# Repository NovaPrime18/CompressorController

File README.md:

# Mains Powered Motor Driver

> **HVAC VESC** — A mains-powered, VESC-compatible three-phase motor driver with active Power Factor Correction, built for compressor and HVAC applications.

---

<table><tr>
<td></td>
<td></td>
</tr></table>

---

## Overview

This project is an open-hardware, mains-powered (230 V AC) three-phase motor driver that is fully compatible with the [VESC firmware](https://vesc-project.com/) ecosystem. It targets compressor and HVAC drive applications and is designed with grid compliance in mind, featuring active Power Factor Correction (PFC) to meet IEC 61000-3-2 harmonic emission limits.

The board takes 230 V AC directly from the mains, rectifies it to a high-voltage DC bus, and drives a three-phase motor through an Infineon IKCM10H60 Intelligent Power Module. A VESC Express (ESP32) module provides wireless connectivity and acts as the CAN/Wi-Fi/BT bridge, while an STM32F405 runs the VESC motor-control firmware.

---

## Key Features

| Feature | Details |
|---|---|
| **Input** | 230 V AC single-phase mains |
| **HV Bus** | Rectified DC bus (~325 V DC nominal) |
| **Power Bridge** | Infineon `IKCM10H60GAXKMA1` IPM — 10 A / 600 V, integrated gate drivers & bootstrap |
| **Active PFC** | Texas Instruments `UCC28180D` — CCM PFC controller |
| **MCU** | STMicroelectronics `STM32F405RGTx` running VESC firmware |
| **Connectivity** | VESC Express (ESP32) — Wi-Fi, Bluetooth & CAN bridge |
| **USB** | USB Type-C (programming / configuration) |
| **CAN Bus** | Dual isolated CAN interfaces |
| **Debug** | Tag-Connect SWD header |
| **Status LEDs** | Red & Green indicators |
| **License** | CERN Open Hardware Licence v2 |

---

## Block Diagram

```
         230 V AC
             │
     ┌───────▼────────┐
     │   Power in     │  EMI filter, inrush, rectifier
     │  (powerin.sch) │
     └───────┬────────┘
             │ HV DC Bus (~325 V)
     ┌───────▼────────┐
     │   Active PFC   │  UCC28180D — CCM boost PFC
     │   (pfc.sch)    │  IEC 61000-3-2 compliant
     └───────┬────────┘
             │ Regulated HV Bus
     ┌───────▼────────┐
     │  3-Phase IPM   │  IKCM10H60GAXKMA1
     │  (phases.sch)  │  10 A / 600 V, 3-phase bridge
     └───────┬────────┘
             │ U / V / W
          Motor / Compressor

     ┌──────────────────────────────────────────┐
     │              Control Domain              │
     │                                          │
     │  STM32F405  ◄──►  Isolator  ◄──►  IPM   │
     │  (VESC FW)        (iso.sch)    gate sigs │
     │      │                                   │
     │  Filters ── Current U/V/W sensing        │
     │  (filters)  Bus voltage / Phase voltages │
     │      │                                   │
     │  VESC Express (ESP32) ── CAN / BT / WiFi │
     │  LV Power ── 3.3 V / 5 V rails          │
     └──────────────────────────────────────────┘
```

---

## Schematic Hierarchy

The design is split into focused sub-sheets for clarity and reuse:

| Sheet | File | Description |
|---|---|---|
| Top-level | `CompressorController.kicad_sch` | Connectors, indicators, sheet assembly |
| MCU | `MCU.kicad_sch` | STM32F405RGTx, crystal, decoupling, SWD |
| PFC | `pfc.kicad_sch` | UCC28180D active PFC stage |
| Power in | `powerin.kicad_sch` | Mains input, EMI filter, bridge rectifier |
| Phases | `phases.kicad_sch` | IKCM10H60 IPM, current sensing |
| Filters | `filters.kicad_sch` | ADC anti-aliasing for current & voltage signals |
| Isolator | `isolator.kicad_sch` | Gate-signal and fault isolation barrier |
| LV Power | `lvpower.kicad_sch` | 3.3 V / 5 V low-voltage power supply |
| WiFi & BT | `express.kicad_sch` | VESC Express (ESP32) module |
| CAN | `can.kicad_sch` | Isolated CAN transceivers |

---

## Firmware

This board is designed to run the open-source **VESC firmware** and is configurable via **VESC Tool**.

- [VESC Firmware](https://github.com/vedderb/bldc)
- [VESC Tool](https://vesc-project.com/vesc_tool)

Motor parameters, PID gains, current limits, and field-weakening are all configured through VESC Tool over USB-C or wirelessly via the onboard VESC Express (Wi-Fi / BLE).

---

## Regulatory Compliance Targets

This design is being developed with the following standards in scope:

| Standard | Scope |
|---|---|
| **IEC 61000-3-2** | Harmonic current emission limits *(primary — addressed by active PFC)* |
| **IEC 60335-2-34** | Particular requirements for motor-compressors |
| **EN IEC 63000** | RoHS technical documentation |

> ⚠️ **Note:** This is an open hardware design. Regulatory certification (CE marking) must be obtained by the integrating party before placing the product on the EU market. The presence of PFC significantly aids IEC 61000-3-2 Class A/D compliance but does not guarantee it without verified measurement.

---

## Safety Warnings

> **⚡ HIGH VOLTAGE — MAINS POWERED**
>
> This board operates at lethal voltages. The HV DC bus reaches approximately **325–400 V DC** from rectified mains. Do **not** touch the board while powered. Ensure adequate enclosure, creepage/clearance distances, and fusing when integrating into a product. Only qualified persons should work on mains-connected equipment.

---

## License

This project is released under the **CERN Open Hardware Licence Version 2 – Strongly Reciprocal (CERN-OHL-S v2)**.

You may study, modify, and distribute this design, provided that any derivative works are released under the same licence and that attribution to the original authors is maintained.

© Picobello B.V. — see [`LICENSE`](LICENSE) for full terms.

---

## Contributing

Issues, improvements, and pull requests are welcome. Please open an issue before submitting large changes so the direction can be aligned first.

When contributing hardware changes, include updated schematics (KiCad 10 `.kicad_sch` format) and a description of what was changed and why.

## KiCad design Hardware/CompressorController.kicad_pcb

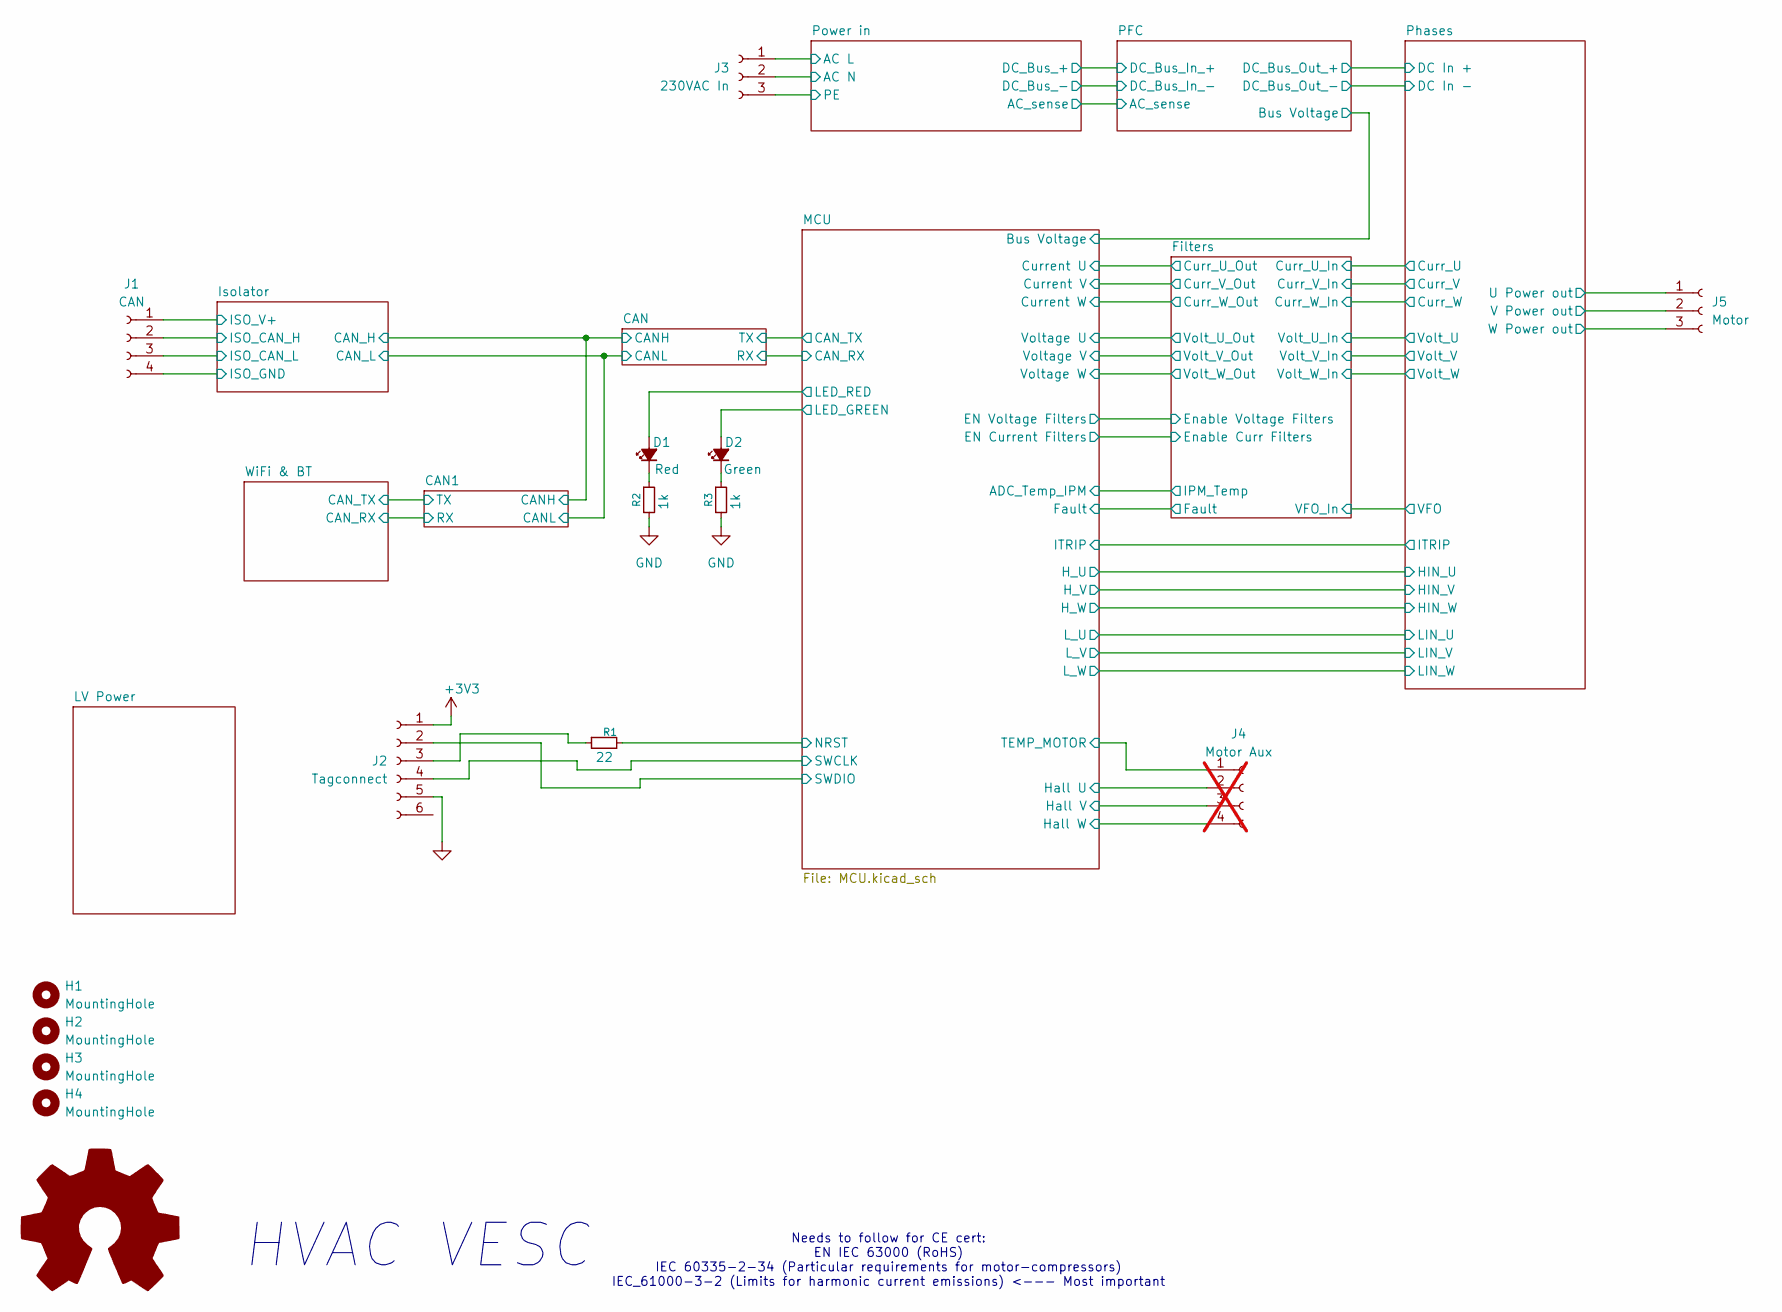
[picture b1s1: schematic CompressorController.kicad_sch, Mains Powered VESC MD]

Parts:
D1: Red; LED_0603_1608Metric; LCSC C2286
D2: Green; LED_0603_1608Metric; LCSC C84267
H1, H2, H3, H4: MountingHole; MountingHole_3.2mm_M3
J1: CAN; PhoenixContact_MC_1,5_4-G-3.5_1x04_P3.50mm_Horizontal; JLC C395831
J2: Tagconnect; Tag-Connect_TC2030-IDC-NL_2x03_P1.27mm_Vertical
J3: 230VAC In; PhoenixContact_GMSTB_2,5_3-GF-7,62_1x03_P7.62mm_Horizontal_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; JLC C5121957
J4: Motor Aux; PhoenixContact_MC_1,5_4-G-3.5_1x04_P3.50mm_Horizontal; JLC C395831; not fitted
J5: Motor; PhoenixContact_GMSTB_2,5_3-GF-7,62_1x03_P7.62mm_Horizontal_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; JLC C5121957
R1: 22; R_0603_1608Metric; LCSC C23345
R2, R3: 1k; R_0603_1608Metric; LCSC C21190

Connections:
+3V3: J2.1; also elsewhere on the board
/Isolator/ISO_CAN_H: J1.2; also elsewhere on the board
/Isolator/ISO_CAN_L: J1.3; also elsewhere on the board
/Isolator/ISO_GND: J1.4; also elsewhere on the board
/Isolator/ISO_V+: J1.1; also elsewhere on the board
/MCU/LED_GREEN: D2.2 (A); also elsewhere on the board
/MCU/LED_RED: D1.2 (A); also elsewhere on the board
/MCU/NRST: R1.2; also elsewhere on the board
/MCU/SWCLK: J2.4; also elsewhere on the board
/MCU/SWDIO: J2.2; also elsewhere on the board
/Phases/U Power out: J5.1; also elsewhere on the board
/Phases/V Power out: J5.2; also elsewhere on the board
/Phases/W Power out: J5.3; also elsewhere on the board
/Power in/AC L: J3.1; also elsewhere on the board
/Power in/AC N: J3.2; also elsewhere on the board
Earth_Protective: J3.3; also elsewhere on the board
GND: J2.5, R2.2, R3.2; also elsewhere on the board
unnamed: D1.1 (K), R2.1
unnamed: D2.1 (K), R3.1
unnamed: J2.3, R1.1

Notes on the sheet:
HVAC VESC
Needs to follow for CE cert: EN IEC 63000 (RoHS) IEC 60335-2-34 (Particular requirements for motor-compressors) IEC_61000-3-2 (Limits for harmonic current emissions) <--- Most important

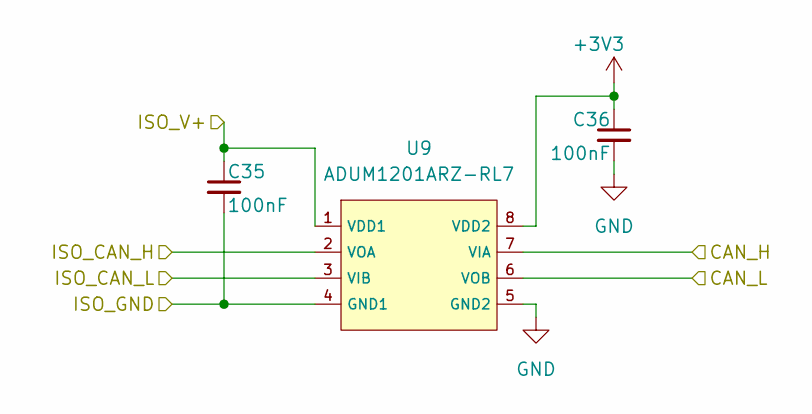
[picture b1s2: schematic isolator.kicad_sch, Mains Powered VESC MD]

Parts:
C35, C36: 100nF; C_0603_1608Metric; LCSC C14663
U9: ADUM1201ARZ-RL7; SOIC-8_L4.9-W3.9-P1.27-LS6.0-BL; Part ADUM1201ARZ-RL7; LCSC C9669

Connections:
+3V3: C36.1, U9.8 (VDD2); also elsewhere on the board
/CAN/CANH: U9.7 (VIA); also elsewhere on the board
/CAN/CANL: U9.6 (VOB); also elsewhere on the board
/Isolator/ISO_CAN_H: U9.2 (VOA); also elsewhere on the board
/Isolator/ISO_CAN_L: U9.3 (VIB); also elsewhere on the board
/Isolator/ISO_GND: C35.2, U9.4 (GND1); also elsewhere on the board
/Isolator/ISO_V+: C35.1, U9.1 (VDD1); also elsewhere on the board
GND: C36.2, U9.5 (GND2); also elsewhere on the board

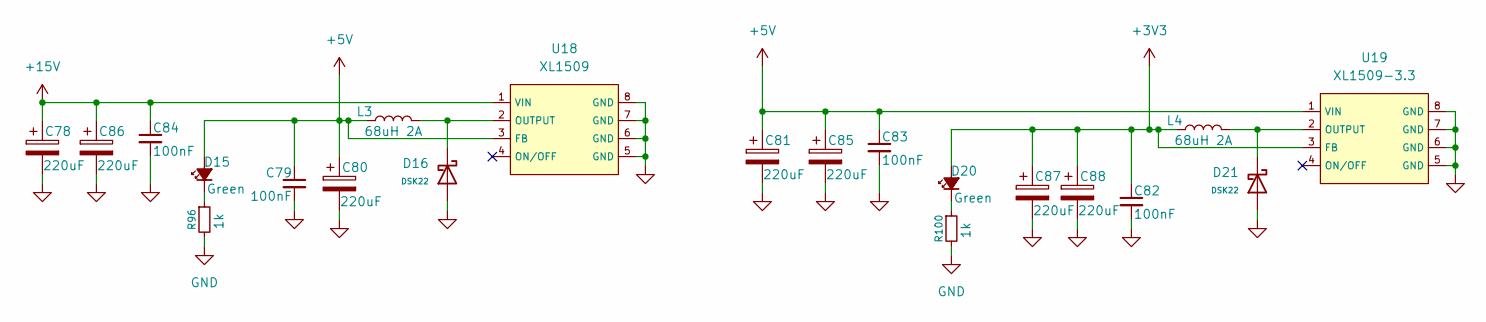
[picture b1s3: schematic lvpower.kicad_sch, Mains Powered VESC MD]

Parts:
C78, C80, C81, C85, C86, C87, C88: 220uF; CP_Elec_8x10.5; Voltage 50V; JLC C3340
C79, C82, C83, C84: 100nF; C_0603_1608Metric; LCSC C14663
D15, D20: Green; LED_0603_1608Metric; LCSC C84267
D16, D21: DSK22; D_SOD-123FL; Forward Voltage (Vf@If) 550mV@2A; Reverse Voltage (Vr) 20V; Part DSK22; LCSC C28646290
L3, L4: 68uH 2A; L_KOHERelec_MDA7030; JLC C2894721
R96, R100: 1k; R_0603_1608Metric; LCSC C21190
U18: XL1509; SOIC-8_L5.0-W4.0-P1.27-LS6.0-BL; Output Voltage 5V; Input Voltage 4.5V~40V; Part XL1509-5.0E1; LCSC C61063
U19: XL1509-3.3; SOIC-8_L5.0-W4.0-P1.27-LS6.0-BL; Output Voltage 3.3V; Input Voltage 4.5V~40V; Part XL1509-5.0E1; LCSC C2681226

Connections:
+3V3: C82.1, C87.1, C88.1, D20.2 (A), L4.1, U19.3 (FB); also elsewhere on the board
+5V: C79.1, C80.1, C81.1, C83.1, C85.1, D15.2 (A), L3.1, U18.3 (FB), U19.1 (VIN); also elsewhere on the board
+15V: C78.1, C84.1, C86.1, U18.1 (VIN); also elsewhere on the board
GND: C78.2, C79.2, C80.2, C81.2, C82.2, C83.2, C84.2, C85.2, C86.2, C87.2, C88.2, D16.2, D21.2, R96.2, R100.2, U18.5 (GND), U18.6 (GND), U18.7 (GND), U18.8 (GND), U19.5 (GND), U19.6 (GND), U19.7 (GND), U19.8 (GND); also elsewhere on the board
unnamed: D15.1 (K), R96.1
unnamed: D20.1 (K), R100.1
unnamed: D16.1, L3.2, U18.2 (OUTPUT)
unnamed: D21.1, L4.2, U19.2 (OUTPUT)

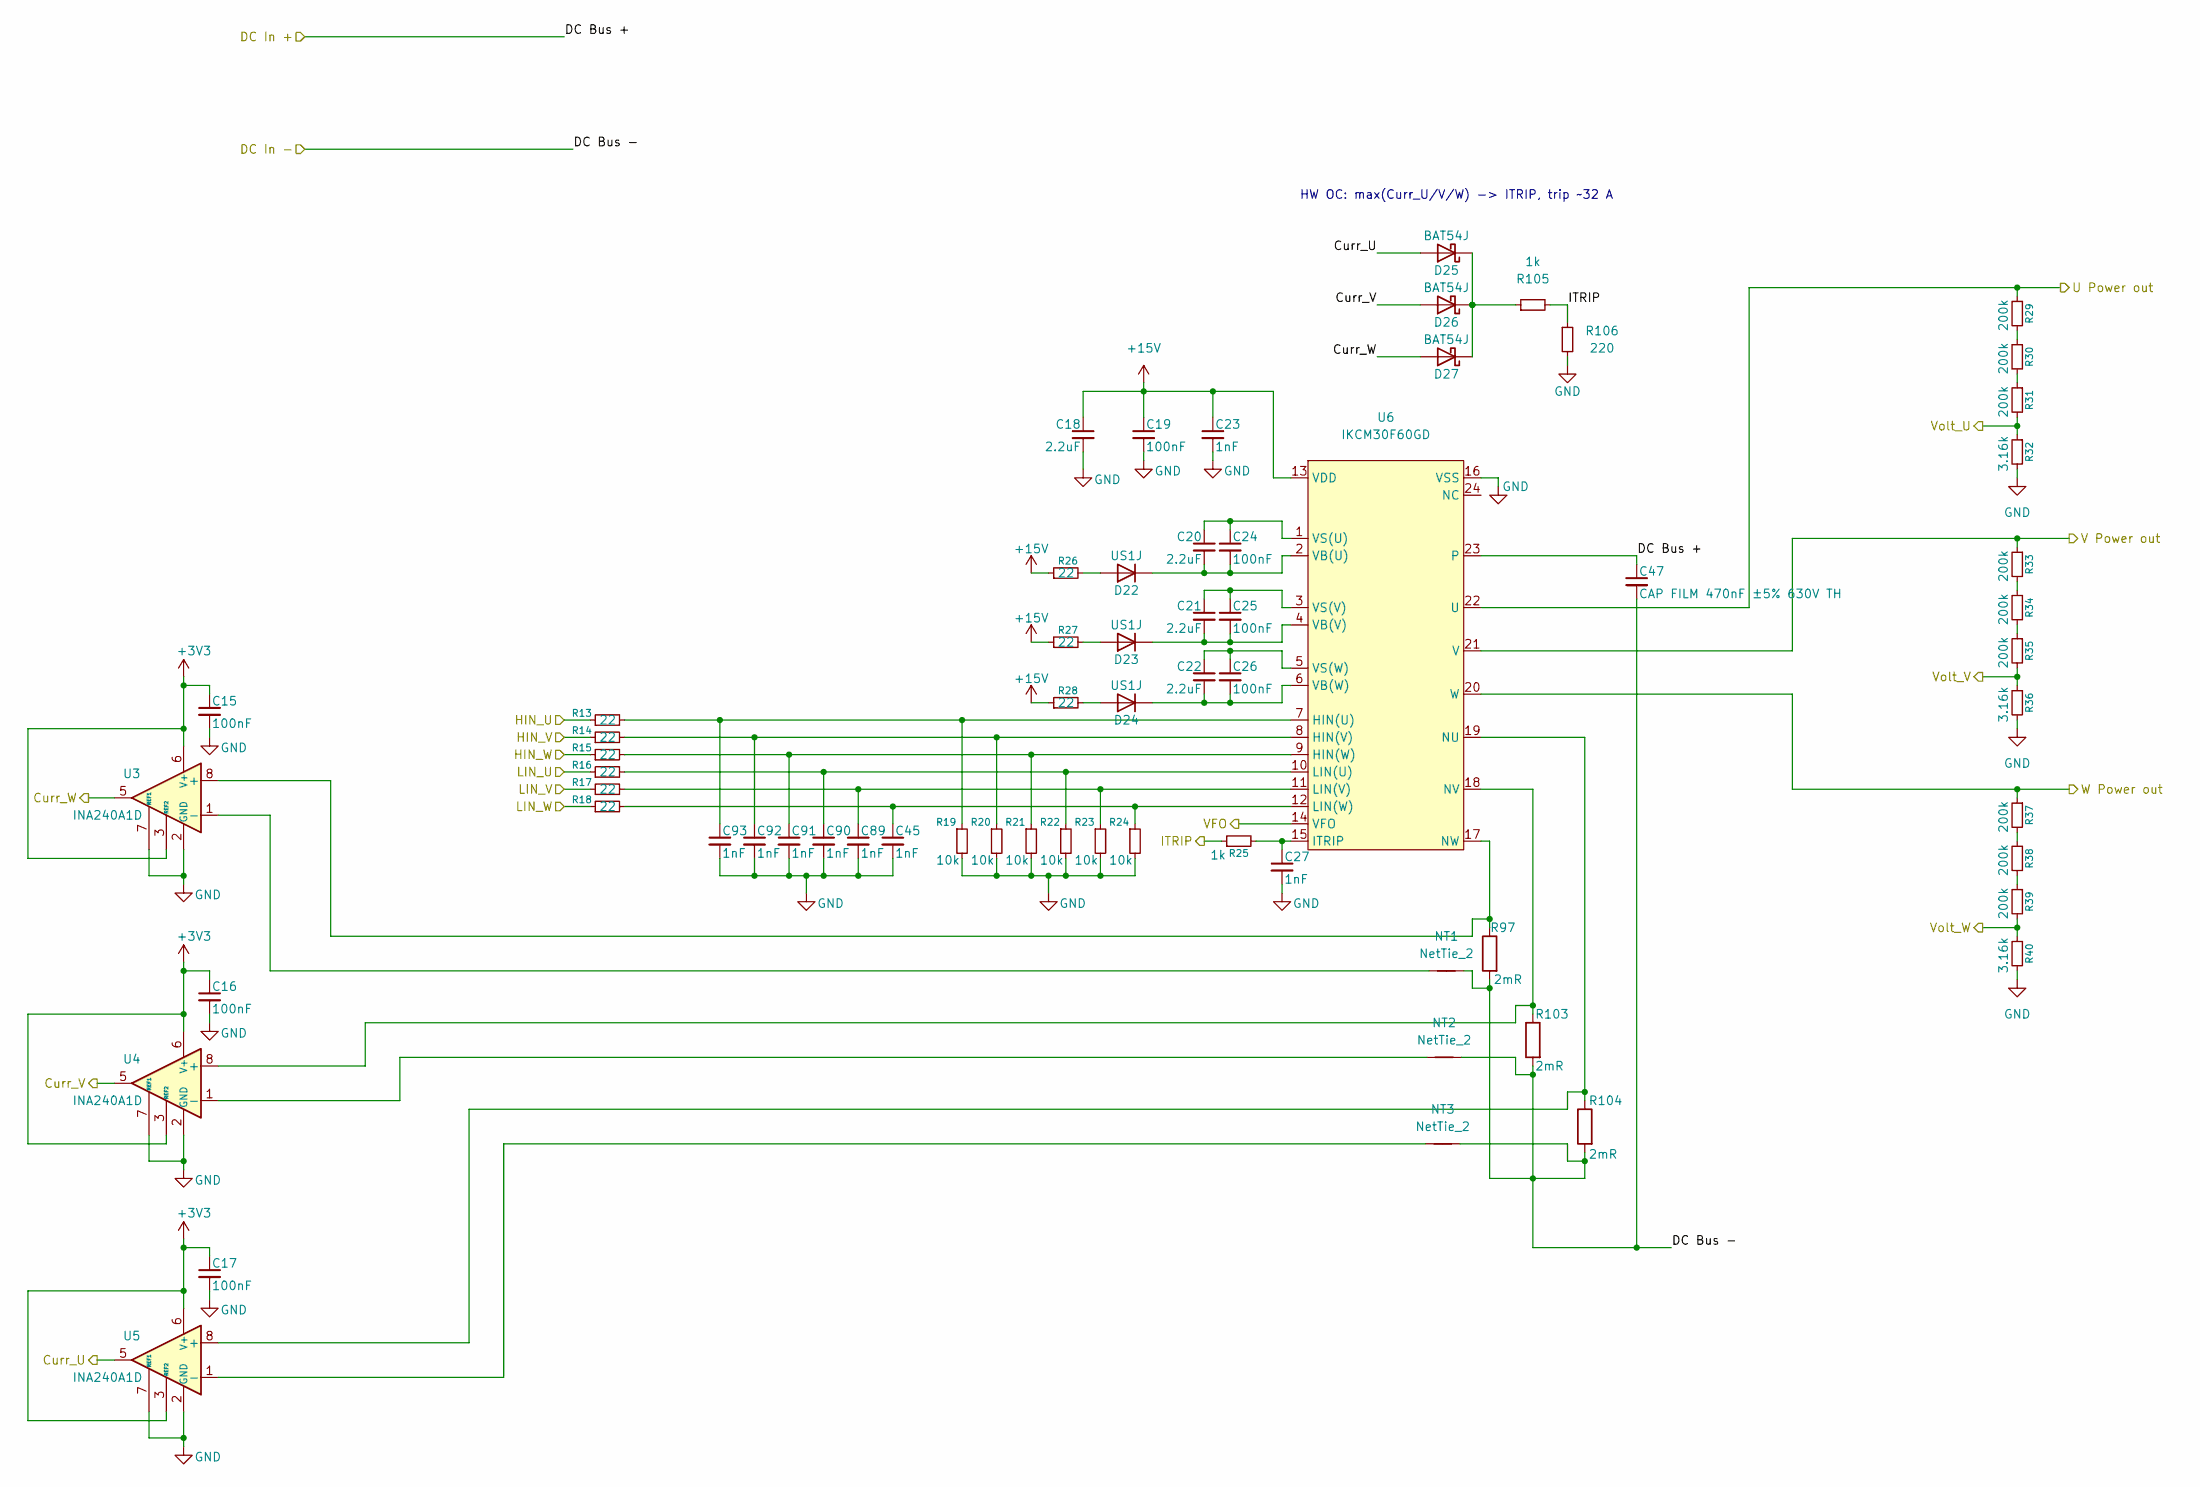
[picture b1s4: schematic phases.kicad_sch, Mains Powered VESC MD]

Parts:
C15, C16, C17, C19, C24, C25, C26: 100nF; C_0603_1608Metric; LCSC C14663
C18, C20, C21, C22: 2.2uF; C_1206_3216Metric; LCSC C50254
C23, C27, C45, C89, C90, C91, C92, C93: 1nF; C_0603_1608Metric; LCSC C1588
C47: CAP FILM 470nF ±5% 630V TH; C_Rect_L26.5mm_W11.5mm_P22.50mm_MKS4; Voltage 630V; LCSC C3796047
D22, D23, D24: US1J; D_SMA; LCSC C44763
D25, D26, D27: BAT54J; D_SOD-323F; LCSC C12744
NT1, NT2, NT3: NetTie_2; NetTie-2_SMD_Pad0.5mm
R13, R14, R15, R16, R17, R18, R26, R27, R28: 22; R_0603_1608Metric; LCSC C23345
R19, R20, R21, R22, R23, R24: 10k; R_0603_1608Metric; LCSC C25804
R25, R105: 1k; R_0603_1608Metric; LCSC C21190
R29, R30, R31, R33, R34, R35, R37, R38, R39: 200k; R_1206_3216Metric; LCSC C17954
R32, R36, R40: 3.16k; R_0805_2012Metric; LCSC C52603
R97, R103, R104: 2mR; R_1206_3216Metric; JLC C2904210
R106: 220; R_0603_1608Metric; LCSC C22962
U3, U4, U5: INA240A1D; SOIC-8_3.9x4.9mm_P1.27mm; LCSC C1346458
U6: IKCM30F60GD; DIP-24_L36.0-W21.0-P1.60-LS28.6-TL; LCSC Part C476130

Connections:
+3V3: C15.1, C16.1, C17.1, U3.3 (REF2), U3.6 (V+), U4.3 (REF2), U4.6 (V+), U5.3 (REF2), U5.6 (V+); also elsewhere on the board
+15V: C18.1, C19.1, C23.1, R26.1, R27.1, R28.1, U6.13 (VDD); also elsewhere on the board
/Filters/VFO_In: U6.14 (VFO); also elsewhere on the board
/Filters/Volt_U_In: R31.2, R32.1; also elsewhere on the board
/Filters/Volt_V_In: R35.2, R36.1; also elsewhere on the board
/Filters/Volt_W_In: R39.2, R40.1; also elsewhere on the board
/MCU/H_U: R13.1; also elsewhere on the board
/MCU/H_V: R14.1; also elsewhere on the board
/MCU/H_W: R15.1; also elsewhere on the board
/MCU/L_U: R16.1; also elsewhere on the board
/MCU/L_V: R17.1; also elsewhere on the board
/MCU/L_W: R18.1; also elsewhere on the board
/Phases/Curr_U: D25.2 (A), U5.5; also elsewhere on the board
/Phases/Curr_V: D26.2 (A), U4.5; also elsewhere on the board
/Phases/Curr_W: D27.2 (A), U3.5; also elsewhere on the board
/Phases/DC Bus +: C47.1, U6.23; also elsewhere on the board
/Phases/ITRIP: R25.1, R105.2, R106.1; also elsewhere on the board
/Phases/U Power out: R29.1, U6.22 (U); also elsewhere on the board
/Phases/V Power out: R33.1, U6.21 (V); also elsewhere on the board
/Phases/W Power out: R37.1, U6.20 (W); also elsewhere on the board
GND: C15.2, C16.2, C17.2, C18.2, C19.2, C23.2, C27.2, C45.2, C47.2, C89.2, C90.2, C91.2, C92.2, C93.2, NT1.2, NT2.2, NT3.2, R19.2, R20.2, R21.2, R22.2, R23.2, R24.2, R32.2, R36.2, R40.2, R97.2, R103.2, R104.2, R106.2, U3.2 (GND), U3.4 (GND), U3.7 (REF1), U4.2 (GND), U4.4 (GND), U4.7 (REF1), U5.2 (GND), U5.4 (GND), U5.7 (REF1), U6.16 (VSS); also elsewhere on the board
unnamed: D22.2 (A), R26.2
unnamed: C20.2, C24.2, D22.1 (K), U6.2 (VB(U))
unnamed: D23.2 (A), R27.2
unnamed: C21.2, C25.2, D23.1 (K), U6.4 (VB(V))
unnamed: D24.2 (A), R28.2
unnamed: C22.2, C26.2, D24.1 (K), U6.6 (VB(W))
unnamed: D25.1 (K), D26.1 (K), D27.1 (K), R105.1
unnamed: R29.2, R30.1
unnamed: R30.2, R31.1
unnamed: R33.2, R34.1
unnamed: R34.2, R35.1
unnamed: R37.2, R38.1
unnamed: R38.2, R39.1
unnamed: R97.1, U3.8 (+), U6.17 (NW)
unnamed: NT1.1, U3.1 (-)
unnamed: R103.1, U4.8 (+), U6.18 (NV)
unnamed: NT2.1, U4.1 (-)
unnamed: R104.1, U5.8 (+), U6.19 (NU)
unnamed: NT3.1, U5.1 (-)
unnamed: C93.1, R13.2, R19.1, U6.7 (HIN(U))
unnamed: C92.1, R14.2, R20.1, U6.8 (HIN(V))
unnamed: C91.1, R15.2, R21.1, U6.9 (HIN(W))
unnamed: C27.1, R25.2, U6.15 (ITRIP)
unnamed: C90.1, R16.2, R22.1, U6.10 (LIN(U))
unnamed: C89.1, R17.2, R23.1, U6.11 (LIN(V))
unnamed: C45.1, R18.2, R24.1, U6.12 (LIN(W))
unnamed: C20.1, C24.1, U6.1 (VS(U))
unnamed: C21.1, C25.1, U6.3 (VS(V))
unnamed: C22.1, C26.1, U6.5 (VS(W))

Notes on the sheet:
HW OC: max(Curr_U/V/W) -> ITRIP, trip ~32 A

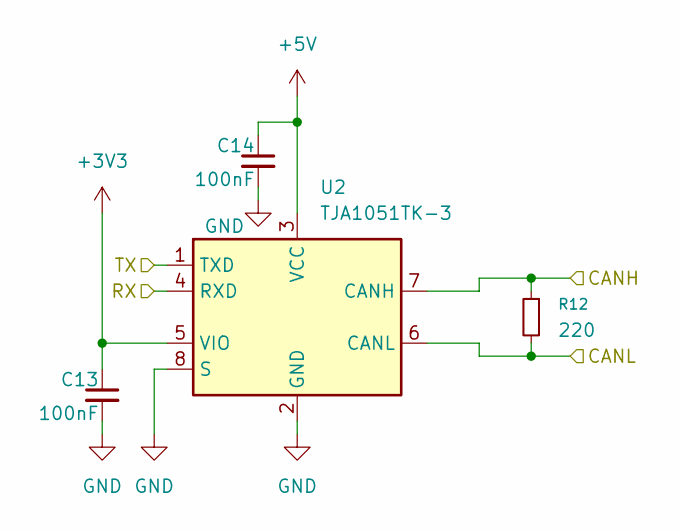
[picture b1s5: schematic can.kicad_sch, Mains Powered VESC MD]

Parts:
C13, C14: 100nF; C_0603_1608Metric; LCSC C14663
R12: 220; R_0603_1608Metric; LCSC C22962
U2: TJA1051TK-3; HVSON-8-1EP_3x3mm_P0.65mm_EP1.6x2.4mm; JLC C2875699

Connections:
+3V3: C13.1, U2.5 (VIO); also elsewhere on the board
+5V: C14.1, U2.3 (VCC); also elsewhere on the board
/CAN1/RX: U2.4 (RXD); also elsewhere on the board
/CAN1/TX: U2.1 (TXD); also elsewhere on the board
/CAN/CANH: R12.1, U2.7 (CANH); also elsewhere on the board
/CAN/CANL: R12.2, U2.6 (CANL); also elsewhere on the board
GND: C13.2, C14.2, U2.2 (GND), U2.8 (S), U2.9 (GND); also elsewhere on the board

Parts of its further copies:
C29, C30: 100nF; C_0603_1608Metric; LCSC C14663
R41: 220; R_0603_1608Metric; LCSC C22962
U7: TJA1051TK-3; HVSON-8-1EP_3x3mm_P0.65mm_EP1.6x2.4mm; JLC C2875699

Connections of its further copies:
+3V3: C29.1, U7.5 (VIO); also elsewhere on the board
+5V: C30.1, U7.3 (VCC); also elsewhere on the board
/CAN/CANH: R41.1, U7.7 (CANH); also elsewhere on the board
/CAN/CANL: R41.2, U7.6 (CANL); also elsewhere on the board
/CAN/RX: U7.4 (RXD); also elsewhere on the board
/CAN/TX: U7.1 (TXD); also elsewhere on the board
GND: C29.2, C30.2, U7.2 (GND), U7.8 (S), U7.9 (GND); also elsewhere on the board

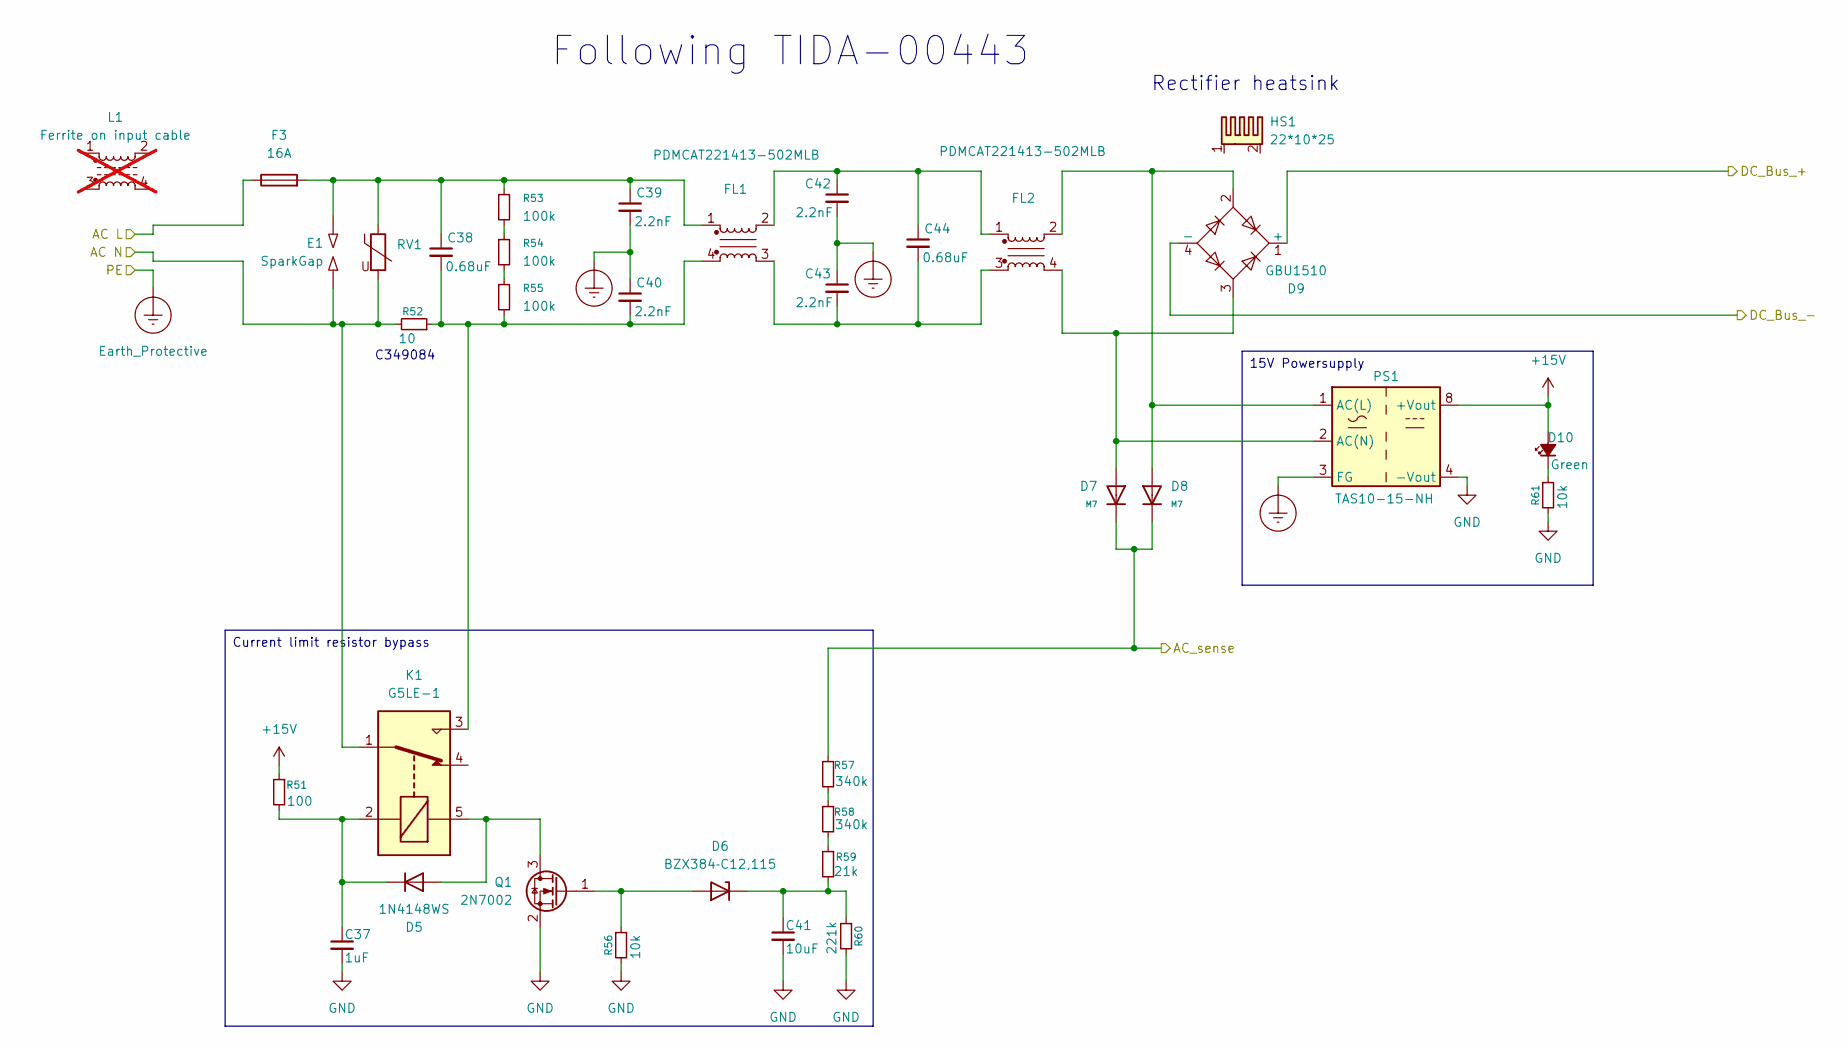
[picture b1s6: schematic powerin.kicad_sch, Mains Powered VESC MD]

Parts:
C37: 1uF; C_0805_2012Metric; LCSC C28323
C38, C44: 0.68uF; C_Rect_L18.0mm_W9.0mm_P15.00mm_FKS3_FKP3; JLC C489081
C39: 2.2nF; C_Disc_D10.5mm_W5.0mm_P7.50mm; JLC C340576
C40, C42, C43: 2.2nF; C_Disc_D10.5mm_W5.0mm_P7.50mm; JLC C2919125
C41: 10uF; C_0805_2012Metric; LCSC C440198
D5: 1N4148WS; D_SOD-323; LCSC C2128
D6: BZX384‐C12,115; D_SOD-323; LCSC C454968
D7, D8: M7; D_SMA; Forward Voltage (Vf@If) 1.1V@1A; Reverse Voltage (Vr) 1kV; Part M7; LCSC C95872
D9: GBU1510; GBU_4P-L22.0-W3.5-P5.08_GBU808; JLC C22447862
D10: Green; LED_0603_1608Metric; LCSC C84267
E1: SparkGap; sparkgap
F3: 16A; FUSE-TH_L29.0-W10.0_XF-103; JLC C41371865
FL1, FL2: PDMCAT221413-502MLB; IND-TH_4P-L28.0-W18.5_C2924777; JLC C2924779
HS1: 22*10*25; HEATSINK-TH_L22.0-W9.8-P14.00-D2.2; JLC C4656
K1: G5LE-1; Relay_SPDT_Omron-G5LE-1; LCSC C116964
L1: Ferrite on input cable; not fitted
PS1: TAS10-15-NH; PWRM-TH_TAS10-XX-NH; JLC C570974
Q1: 2N7002; SOT-23; LCSC C8545
R51: 100; R_1206_3216Metric; LCSC C17901
R52: 10; RES-TH_BD9.0-L36.5-P40.50-D0.8; LCSC C349084
R53, R54, R55: 100k; R_1206_3216Metric; LCSC C17900
R56, R61: 10k; R_0603_1608Metric; LCSC C25804
R57, R58: 340k; R_1206_3216Metric; LCSC C2999478
R59: 21k; R_1206_3216Metric; LCSC C2086273
R60: 221k; R_1206_3216Metric; LCSC C872617
RV1: B72214S2271K101; RV_Disc_D12mm_W5.4mm_P7.5mm; JLC C210689

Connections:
+15V: D10.2 (A), PS1.8 (+Vout), R51.1; also elsewhere on the board
/PFC/AC_sense: D7.1, D8.1, R57.1; also elsewhere on the board
/PFC/DC_Bus_In_+: D9.1 (+); also elsewhere on the board
/PFC/DC_Bus_In_-: D9.4 (-); also elsewhere on the board
/Power in/AC L: F3.1; also elsewhere on the board
/Power in/AC N: E1.2, K1.1, R52.2, RV1.2; also elsewhere on the board
Earth_Protective: C39.2, C40.1, C42.2, C43.1, PS1.3 (FG); also elsewhere on the board
GND: C37.2, C41.2, PS1.4 (-Vout), Q1.2 (S), R56.2, R60.2, R61.2; also elsewhere on the board
unnamed: C38.1, C39.1, E1.1, F3.2, FL1.1, R53.1, RV1.1
unnamed: C38.2, C40.2, FL1.4, K1.3, R52.1, R55.2
unnamed: C42.1, C44.1, FL1.2, FL2.1
unnamed: C43.2, C44.2, FL1.3, FL2.3
unnamed: D5.2 (A), K1.5, Q1.3 (D)
unnamed: C37.1, D5.1 (K), K1.2, R51.2
unnamed: D6.2 (A), Q1.1 (G), R56.1
unnamed: C41.1, D6.1 (K), R59.2, R60.1
unnamed: D10.1 (K), R61.1
unnamed: D8.2, D9.2, FL2.2, PS1.1 (AC(L))
unnamed: D7.2, D9.3, FL2.4, PS1.2 (AC(N))
unnamed: R53.2, R54.1
unnamed: R54.2, R55.1
unnamed: R57.2, R58.1
unnamed: R58.2, R59.1

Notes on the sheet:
Rectifier heatsink
C349084
Following TIDA-00443
15V Powersupply
Current limit resistor bypass

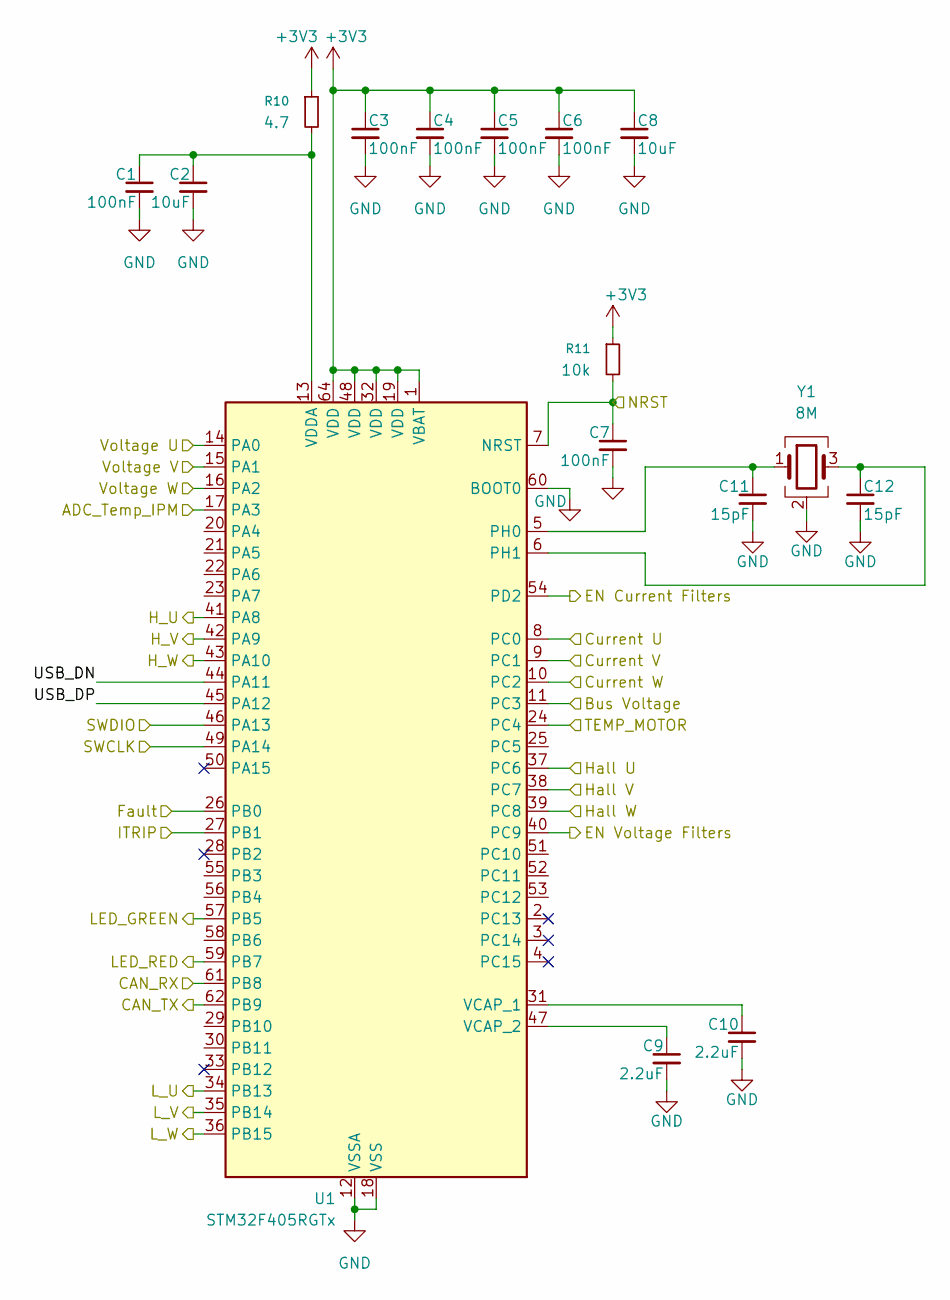
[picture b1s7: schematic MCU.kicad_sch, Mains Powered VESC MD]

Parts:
C1, C3, C4, C5, C6, C7: 100nF; C_0603_1608Metric; LCSC C14663
C2, C8: 10uF; C_0805_2012Metric; LCSC C440198
C9, C10: 2.2uF; C_1206_3216Metric; LCSC C50254
C11, C12: 15pF; C_0603_1608Metric; LCSC C1644
R10: 4.7; R_0603_1608Metric; LCSC C23164
R11: 10k; R_0603_1608Metric; LCSC C25804
U1: STM32F405RGTx; LQFP-64_10x10mm_P0.5mm; LCSC C15742
Y1: 8M; Crystal_SMD_3225-4Pin_3.2x2.5mm; JLC C2682775

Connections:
+3V3: C3.1, C4.1, C5.1, C6.1, C8.1, R10.1, R11.1, U1.1 (VBAT), U1.19 (VDD), U1.32 (VDD), U1.48 (VDD), U1.64 (VDD); also elsewhere on the board
/CAN/RX: U1.61 (PB8); also elsewhere on the board
/CAN/TX: U1.62 (PB9); also elsewhere on the board
/Filters/Curr_U_Out: U1.8 (PC0); also elsewhere on the board
/Filters/Curr_V_Out: U1.9 (PC1); also elsewhere on the board
/Filters/Curr_W_Out: U1.10 (PC2); also elsewhere on the board
/Filters/EN_C: U1.54 (PD2); also elsewhere on the board
/Filters/EN_V: U1.40 (PC9); also elsewhere on the board
/Filters/Fault: U1.26 (PB0); also elsewhere on the board
/Filters/IPM_Temp: U1.17 (PA3); also elsewhere on the board
/Filters/Volt_U_In: U1.14 (PA0); also elsewhere on the board
/Filters/Volt_V_In: U1.15 (PA1); also elsewhere on the board
/Filters/Volt_W_In: U1.16 (PA2); also elsewhere on the board
/MCU/Bus Voltage: U1.11 (PC3); also elsewhere on the board
/MCU/H_U: U1.41 (PA8); also elsewhere on the board
/MCU/H_V: U1.42 (PA9); also elsewhere on the board
/MCU/H_W: U1.43 (PA10); also elsewhere on the board
/MCU/Hall U: U1.37 (PC6)
/MCU/Hall V: U1.38 (PC7)
/MCU/Hall W: U1.39 (PC8)
/MCU/LED_GREEN: U1.57 (PB5); also elsewhere on the board
/MCU/LED_RED: U1.59 (PB7); also elsewhere on the board
/MCU/L_U: U1.34 (PB13); also elsewhere on the board
/MCU/L_V: U1.35 (PB14); also elsewhere on the board
/MCU/L_W: U1.36 (PB15); also elsewhere on the board
/MCU/NRST: C7.1, R11.2, U1.7 (NRST); also elsewhere on the board
/MCU/SWCLK: U1.49 (PA14); also elsewhere on the board
/MCU/SWDIO: U1.46 (PA13); also elsewhere on the board
/MCU/TEMP_MOTOR: U1.24 (PC4)
/MCU/USB_DN: U1.44 (PA11)
/MCU/USB_DP: U1.45 (PA12)
/Phases/ITRIP: U1.27 (PB1); also elsewhere on the board
GND: C1.2, C2.2, C3.2, C4.2, C5.2, C6.2, C7.2, C8.2, C9.2, C10.2, C11.2, C12.2, U1.12 (VSSA), U1.18 (VSS), U1.60 (BOOT0), U1.63 (VSS), Y1.2 (G), Y1.4 (G); also elsewhere on the board
unnamed: C11.1, U1.5 (PH0), Y1.1
unnamed: C12.1, U1.6 (PH1), Y1.3
unnamed: C10.1, U1.31 (VCAP_1)
unnamed: C9.1, U1.47 (VCAP_2)
unnamed: C1.1, C2.1, R10.2, U1.13 (VDDA)

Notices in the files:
README.md:
License: CERN-OHL
